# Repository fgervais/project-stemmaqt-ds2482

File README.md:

# DS2482 Stemma QT Board

## Usage with CircuitPython

Only a couple lines of python are required to make this board appear as a standard
`adafruit_onewire.bus.OneWireBus` object.

See: https://github.com/fgervais/ds2482

## OSHPark

<a href="https://oshpark.com/shared_projects/6VDPQxtW" target="_blank">https://oshpark.com/shared_projects/6VDPQxtW</a>

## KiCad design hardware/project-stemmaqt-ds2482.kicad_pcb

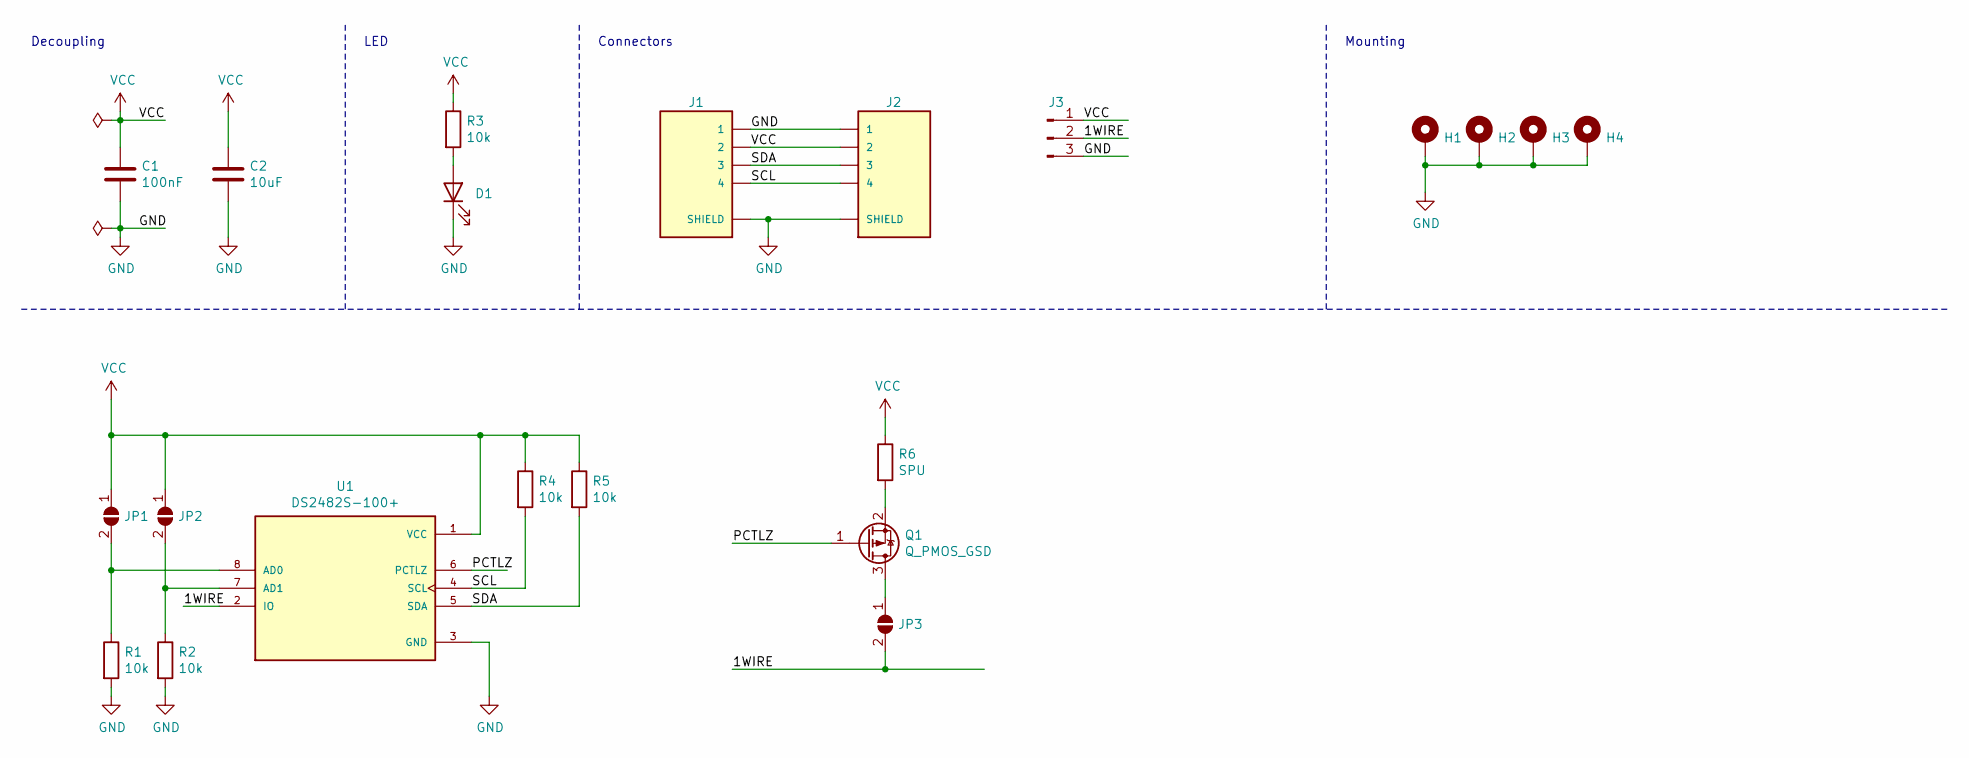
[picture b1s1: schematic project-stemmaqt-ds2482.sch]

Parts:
C1: 100nF; C_0603_1608Metric
C2: 10uF; C_1210_3225Metric
D1: LED; LED_0603_1608Metric
H1, H2, H3, H4: MountingHole_Pad; MountingHole_2.2mm_M2_ISO7380_Pad
J1, J2: SM04B-SRSS-TB(LF)(SN); JST_SM04B-SRSS-TB(LF)(SN)
J3: Conn_01x03_Male; PinHeader_1x03_P2.54mm_Vertical
JP1: AD0; SolderJumper-2_P1.3mm_Open_RoundedPad1.0x1.5mm
JP2: AD1; SolderJumper-2_P1.3mm_Open_RoundedPad1.0x1.5mm
JP3: SPU; SolderJumper-2_P1.3mm_Open_RoundedPad1.0x1.5mm
Q1: Q_PMOS_GSD; SOT-23
R1, R2, R3, R4, R5: 10k; R_0603_1608Metric
R6: SPU; R_0603_1608Metric
U1: DS2482S-100+; SOIC127P600X175-8N

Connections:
/1WIRE: J3.2, JP3.2 (B), U1.2 (IO)
/PCTLZ: Q1.1 (G), U1.6 (PCTLZ)
/SCL: J1.4, J2.4, R4.2, U1.4 (SCL)
/SDA: J1.3, J2.3, R5.2, U1.5 (SDA)
GND: C1.2, C2.2, D1.1 (K), H1.1, H2.1, H3.1, H4.1, J1.1, J1.S1 (SHIELD), J1.S2 (SHIELD), J2.1, J2.S1 (SHIELD), J2.S2 (SHIELD), J3.3, R1.2, R2.2, U1.3 (GND)
unnamed: D1.2 (A), R3.2
unnamed: JP1.2 (B), R1.1, U1.8 (AD0)
unnamed: JP2.2 (B), R2.1, U1.7 (AD1)
unnamed: JP3.1 (A), Q1.3 (D)
unnamed: Q1.2 (S), R6.2
VCC: C1.1, C2.1, J1.2, J2.2, J3.1, JP1.1 (A), JP2.1 (A), R3.1, R4.1, R5.1, R6.1, U1.1 (VCC)

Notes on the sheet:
Decoupling
LED
Connectors
Mounting

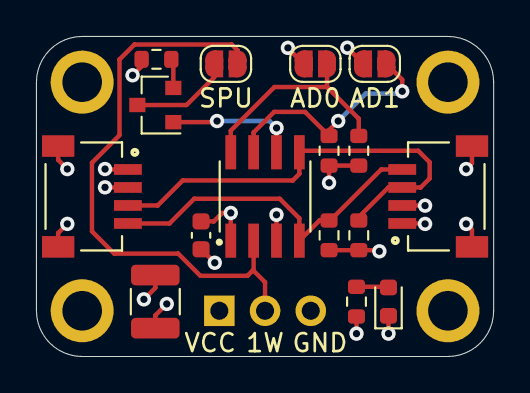
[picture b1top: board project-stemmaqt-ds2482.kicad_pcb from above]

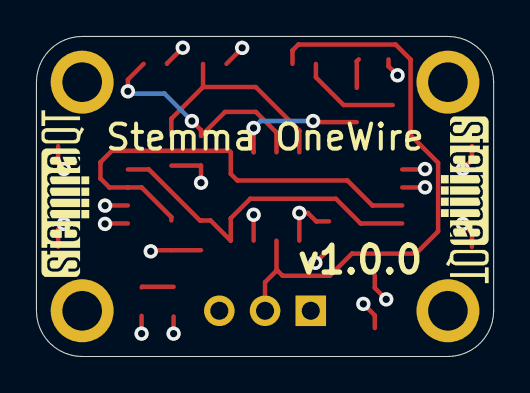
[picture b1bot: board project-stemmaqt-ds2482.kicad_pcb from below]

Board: 4 copper layers, 25.4 x 17.8 mm, 23 parts (2 on the bottom side), 11 nets.

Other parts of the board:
U$30, U$31: STEMMAQT

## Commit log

2021-08-31 New project
2021-08-31 First draft
2021-08-31 Schematic annotation
2021-09-01 Little schematic cleanup
2021-09-01 Annotation
2021-09-02 Placement draft
2021-09-03 First placement done
2021-09-03 Switch to 4 layers
2021-09-03 Routing done
2021-09-04 Add version of previous commit
2021-10-03 Generate assembly file
2021-10-04 Add CircuitPython usage
2021-10-04 Fix board image colors
